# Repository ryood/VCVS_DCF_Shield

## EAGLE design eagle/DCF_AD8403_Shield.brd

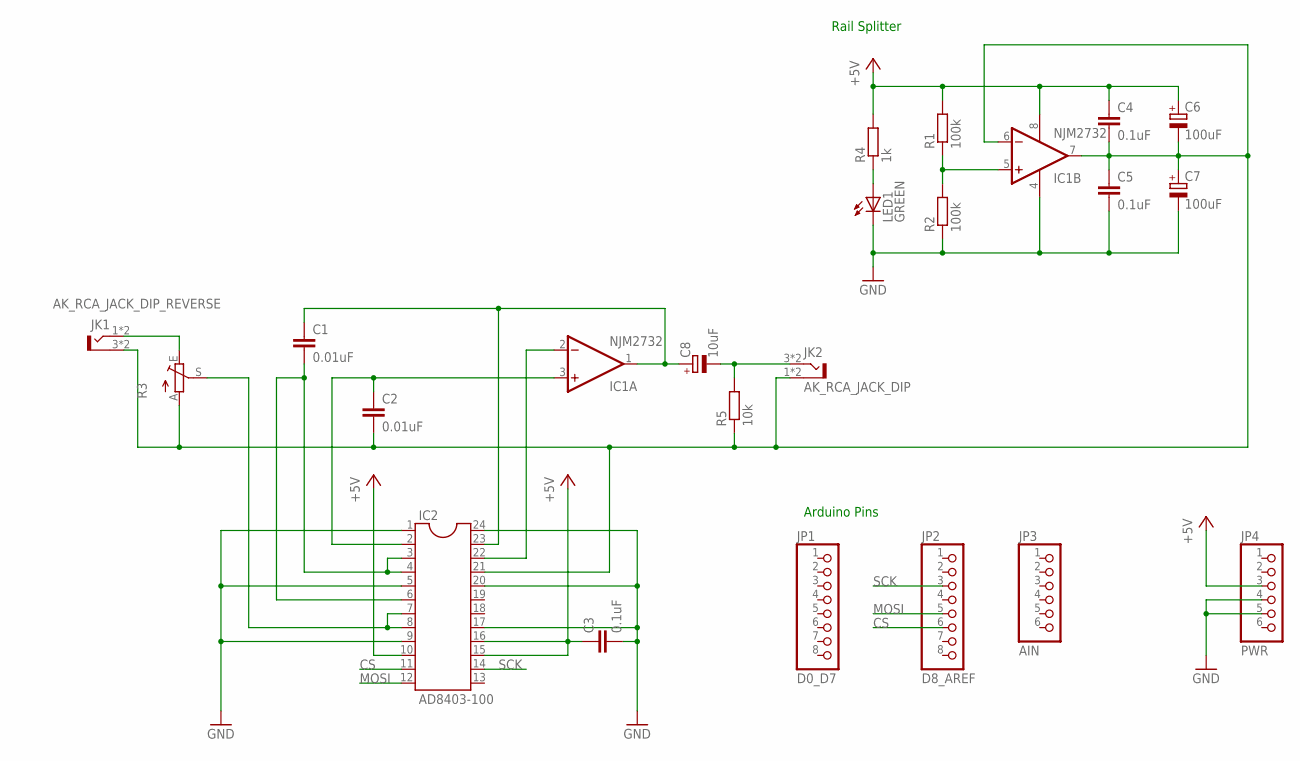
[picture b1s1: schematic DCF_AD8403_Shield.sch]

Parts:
C1, C2: 0.01uF; C050-030X075
C3, C4, C5: 0.1uF; C025-024X044
C6, C7: 100uF; E2,5-6
C8: 10uF; E5-6
IC1: NJM2732; DIL08
IC2: AD8403-100; DIL24-6
JK1: AK_RCA_JACK_DIP_REVERSE; AK_RCA_JACK_DIP
JK2: AK_RCA_JACK_DIP
JP1: D0_D7; 1X08
JP2: D8_AREF; 1X08
JP3: AIN; 1X06
JP4: PWR; 1X06
LED1: GREEN; LED3MM
R1, R2: 100k; 0207/7
R3: TRIM_EU-B25P; B25P
R4: 1k; 0204/7
R5: 10k; 0204/7

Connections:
+5V: C3.1, C4.1, C6.+, IC1.8 (V+), IC2.10, IC2.15, IC2.16, JP4.3, R1.2, R4.2
BYPASS: IC2.7, IC2.8, R3.S
CS: IC2.11, JP2.6
FILTERED: C1.1, C8.+, IC1.1 (OUT), IC2.23
GND: C3.2, C5.2, C7.-, IC1.4 (V-), IC2.1, IC2.5, IC2.9, IC2.17, IC2.20, IC2.24, JP4.4, JP4.5, LED1.K (C), R2.1
MOSI: IC2.12, JP2.5
unnamed: IC1.2 (-IN), IC2.22
unnamed: LED1.A, R4.1
unnamed: C8.-, JK2.3 (T), JK2.4 (T), R5.2
unnamed: IC1.5 (+IN), R1.1, R2.2
unnamed: C1.2, IC2.3, IC2.4, IC2.6
unnamed: JK1.1 (T), JK1.2 (T), R3.E
unnamed: C2.1, IC1.3 (+IN), IC2.2
unnamed: C2.2, C4.2, C5.1, C6.-, C7.+, IC1.6 (-IN), IC1.7 (OUT), IC2.21, JK1.3 (S), JK1.4 (S), JK2.1 (S), JK2.2 (S), R3.A, R5.1
SCK: IC2.14, JP2.3

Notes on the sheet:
Rail Splitter
Arduino Pins

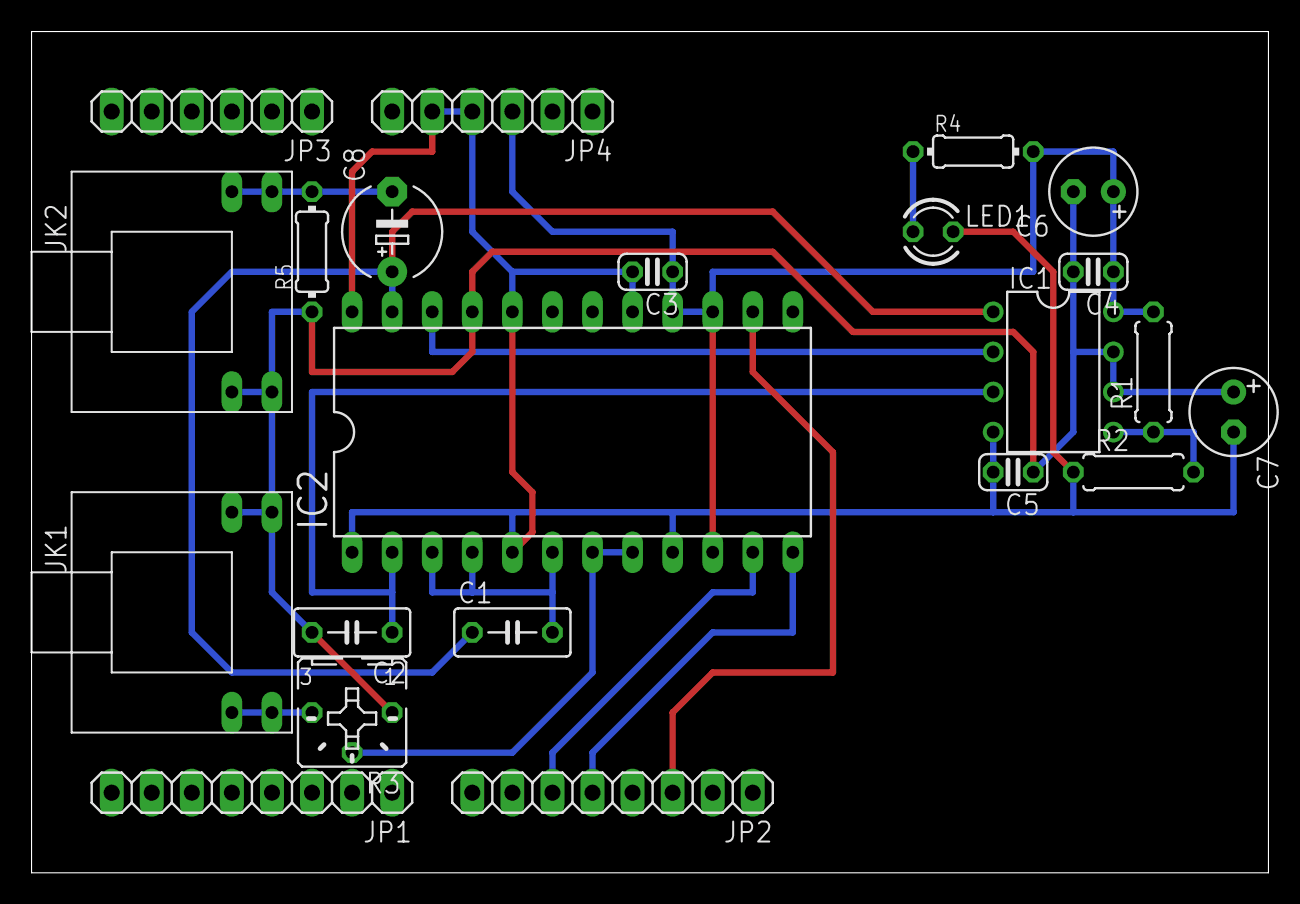
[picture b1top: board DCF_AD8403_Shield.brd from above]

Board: 2 copper layers, 78.4 x 53.3 mm, 22 parts (0 on the bottom side), 15 nets.

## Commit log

2016-04-04 基板図仮配線
2016-04-07 Update Eagle Files
2016-04-07 Add: output AC Coupling
2016-04-07 Remove: Decoupling Capacitor of OPAMP
2016-04-10 Add: OPAMP Decoupling Capacitor
2016-04-13 配線完了
2016-04-13 Add: Input trim pot
2016-04-16 基板図を修正
2016-04-16 fritzingファイルを追加
2016-04-16 テスト表を追加
2016-04-16 Add: VCVS Q Control Test files
2016-04-16 Add: Arduino Sketch
2016-04-16 Add: Schematic & Board PNG files
